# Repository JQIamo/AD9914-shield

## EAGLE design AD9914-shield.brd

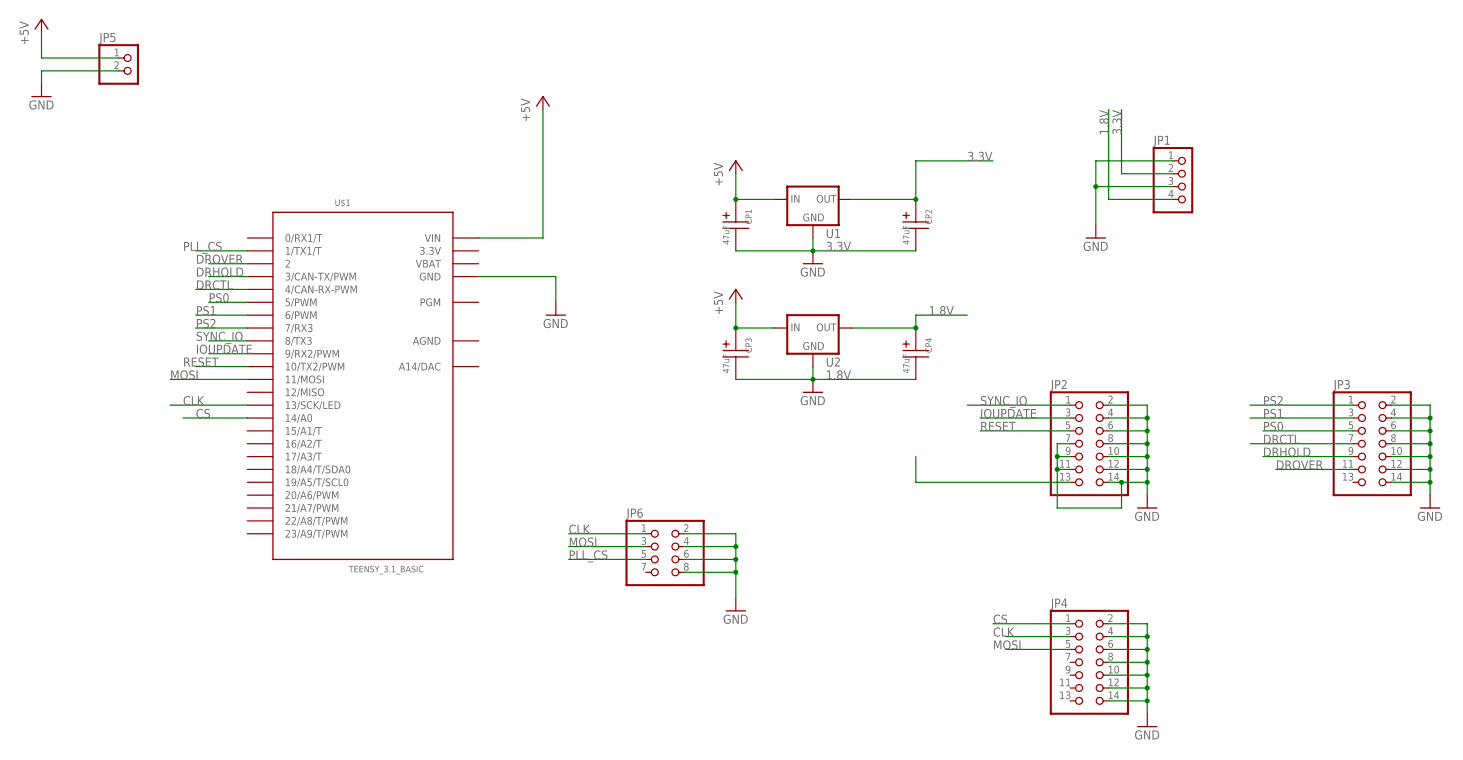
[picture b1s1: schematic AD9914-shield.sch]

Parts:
CP1, CP2, CP3, CP4: 47uF; 2917P
JP1: PINHD-1X4; 1X04
JP2, JP3, JP4: PINHD-2X7; 2X07
JP5: PINHD-1X2; 1X02
JP6: PINHD-2X4; 2X04
U1: 3.3V; SOT223
U2: 1.8V; SOT223
U$1: TEENSY_3.1_BASIC

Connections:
1.8V: CP4.+, JP1.4, U2.2 (OUT), U2.4 (OUT)
3.3V: CP2.+, JP1.2, JP2.13, U1.2 (OUT), U1.4 (OUT), U$1.3.3V, U$1.3.3V1 (3.3V)
+5V: CP1.+, CP3.+, JP5.1, U1.3 (IN), U2.3 (IN), U$1.VIN
AGND: U$1.AGND
CLK: JP4.3, JP6.1, U$1.13 (13/SCK/LED)
CS: JP4.1, U$1.14/A0
DRCTL: JP3.7, U$1.4 (4/CAN-RX-PWM)
DRHOLD: JP3.9, U$1.3 (3/CAN-TX/PWM)
DROVER: JP3.11, U$1.2
GND: CP1.-, CP2.-, CP3.-, CP4.-, JP1.1, JP1.3, JP2.2, JP2.4, JP2.6, JP2.7, JP2.8, JP2.9, JP2.10, JP2.11, JP2.12, JP2.14, JP3.2, JP3.4, JP3.6, JP3.8, JP3.10, JP3.12, JP3.14, JP4.2, JP4.4, JP4.6, JP4.8, JP4.10, JP4.12, JP4.14, JP5.2, JP6.2, JP6.4, JP6.6, JP6.8, U1.1 (GND), U2.1 (GND), U$1.GND, U$1.GND1 (GND)
IOUPDATE: JP2.3, U$1.9 (9/RX2/PWM)
MOSI: JP4.5, JP6.3, U$1.11 (11/MOSI)
PLL_CS: JP6.5, U$1.1 (1/TX1/T)
PS0: JP3.5, U$1.5 (5/PWM)
PS1: JP3.3, U$1.6 (6/PWM)
PS2: JP3.1, U$1.7 (7/RX3)
RESET: JP2.5, U$1.10 (10/TX2/PWM)
SYNC_IO: JP2.1, U$1.8 (8/TX3)
VBAT: U$1.VBAT

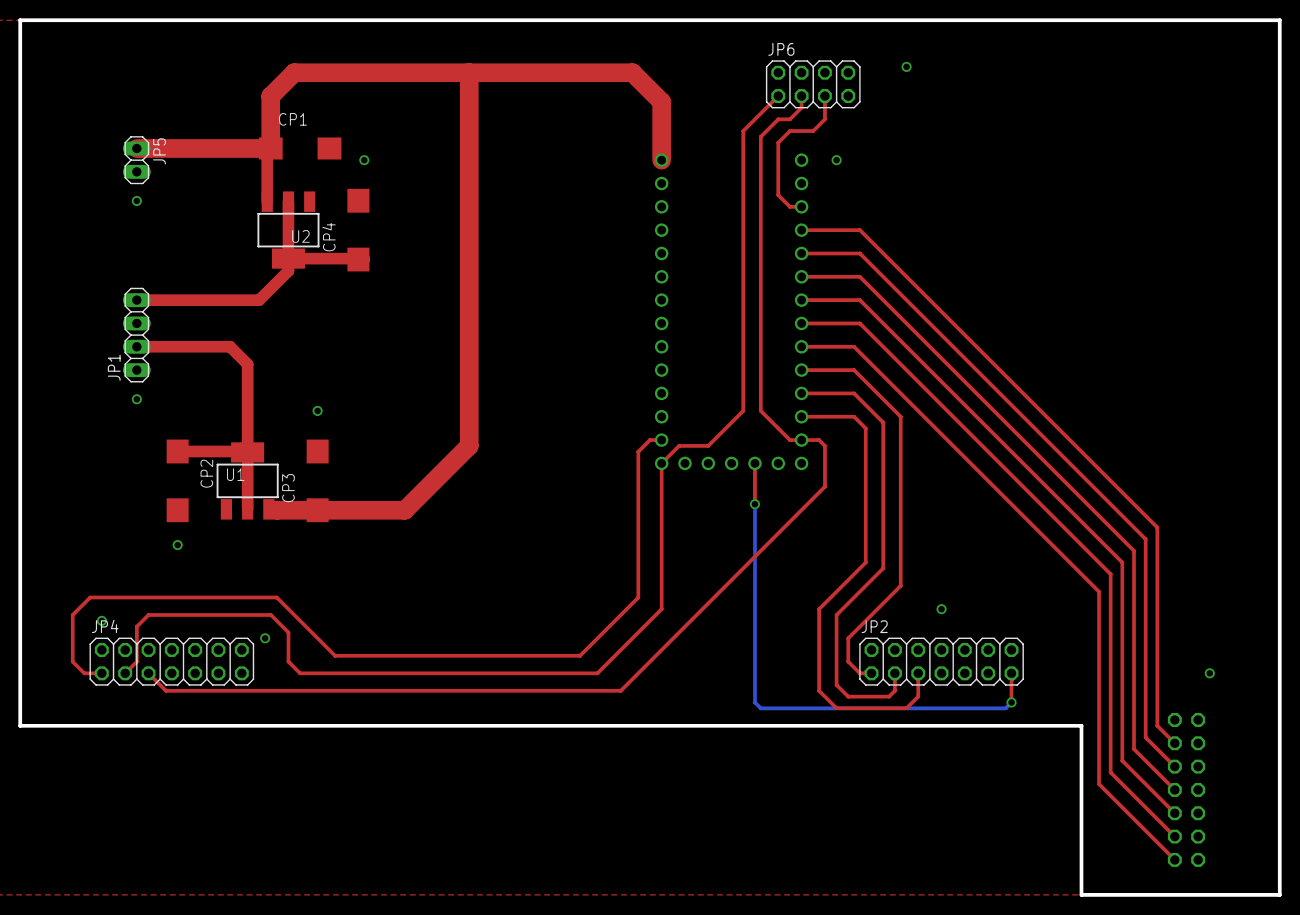
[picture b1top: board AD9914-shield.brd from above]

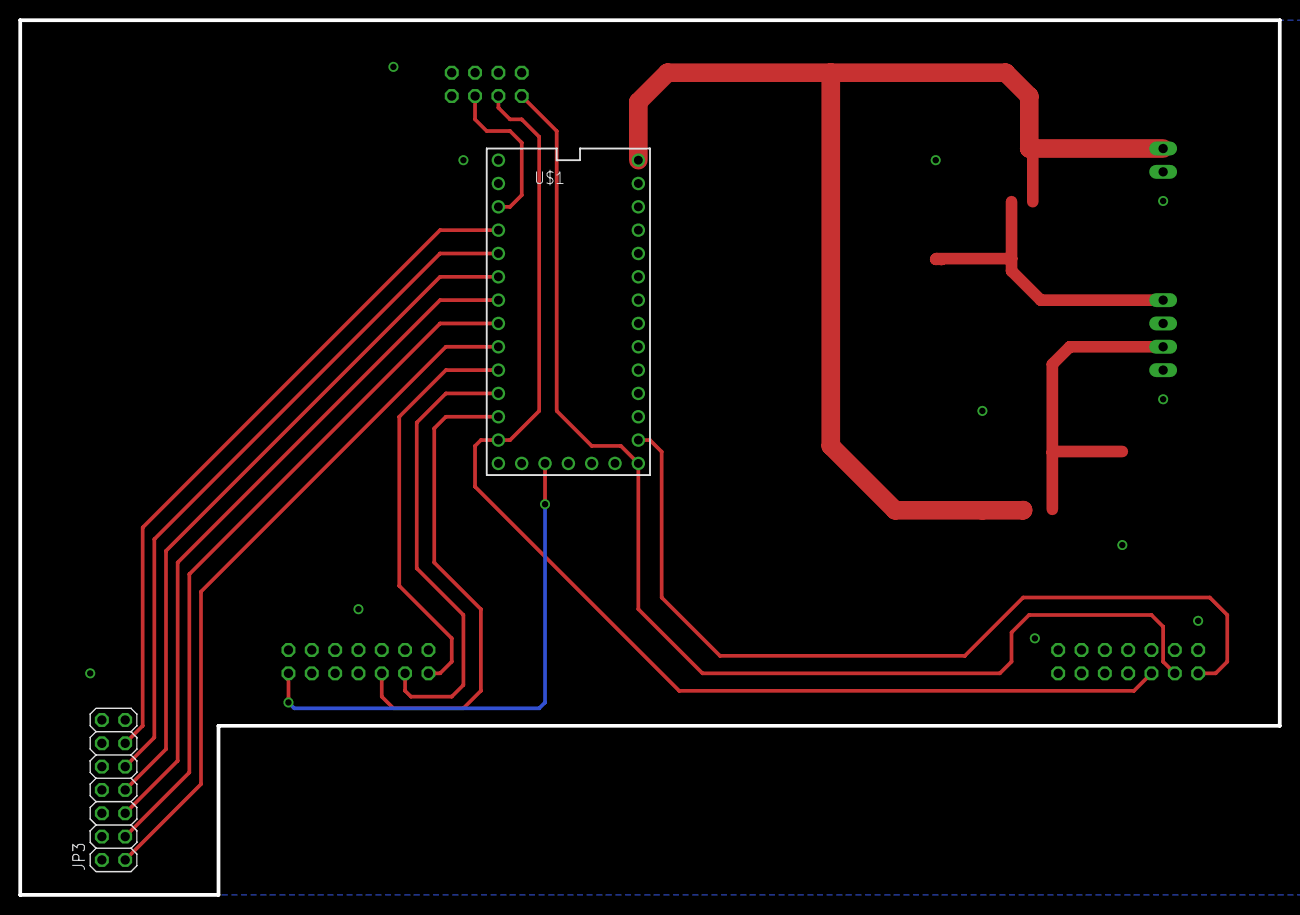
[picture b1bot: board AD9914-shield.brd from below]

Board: 2 copper layers, 137.2 x 95.3 mm, 13 parts (2 on the bottom side), 17 nets.

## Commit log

2016-09-07 initial commit; breakout board for AD9914
    * SPI port
    * Profile select pins
    * DRCTL, DRHOLD, DROVER
    * Jumper for PLL (to supply GHz reference frequency...)
